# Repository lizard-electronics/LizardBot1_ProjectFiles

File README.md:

# LizardBot1_ProjectFiles
## [In Development...]
Project Files for LizardBot 1 differential-drive ROS2 robot.
ROS2 development repository: https://github.com/lizard-electronics/lizardbot1

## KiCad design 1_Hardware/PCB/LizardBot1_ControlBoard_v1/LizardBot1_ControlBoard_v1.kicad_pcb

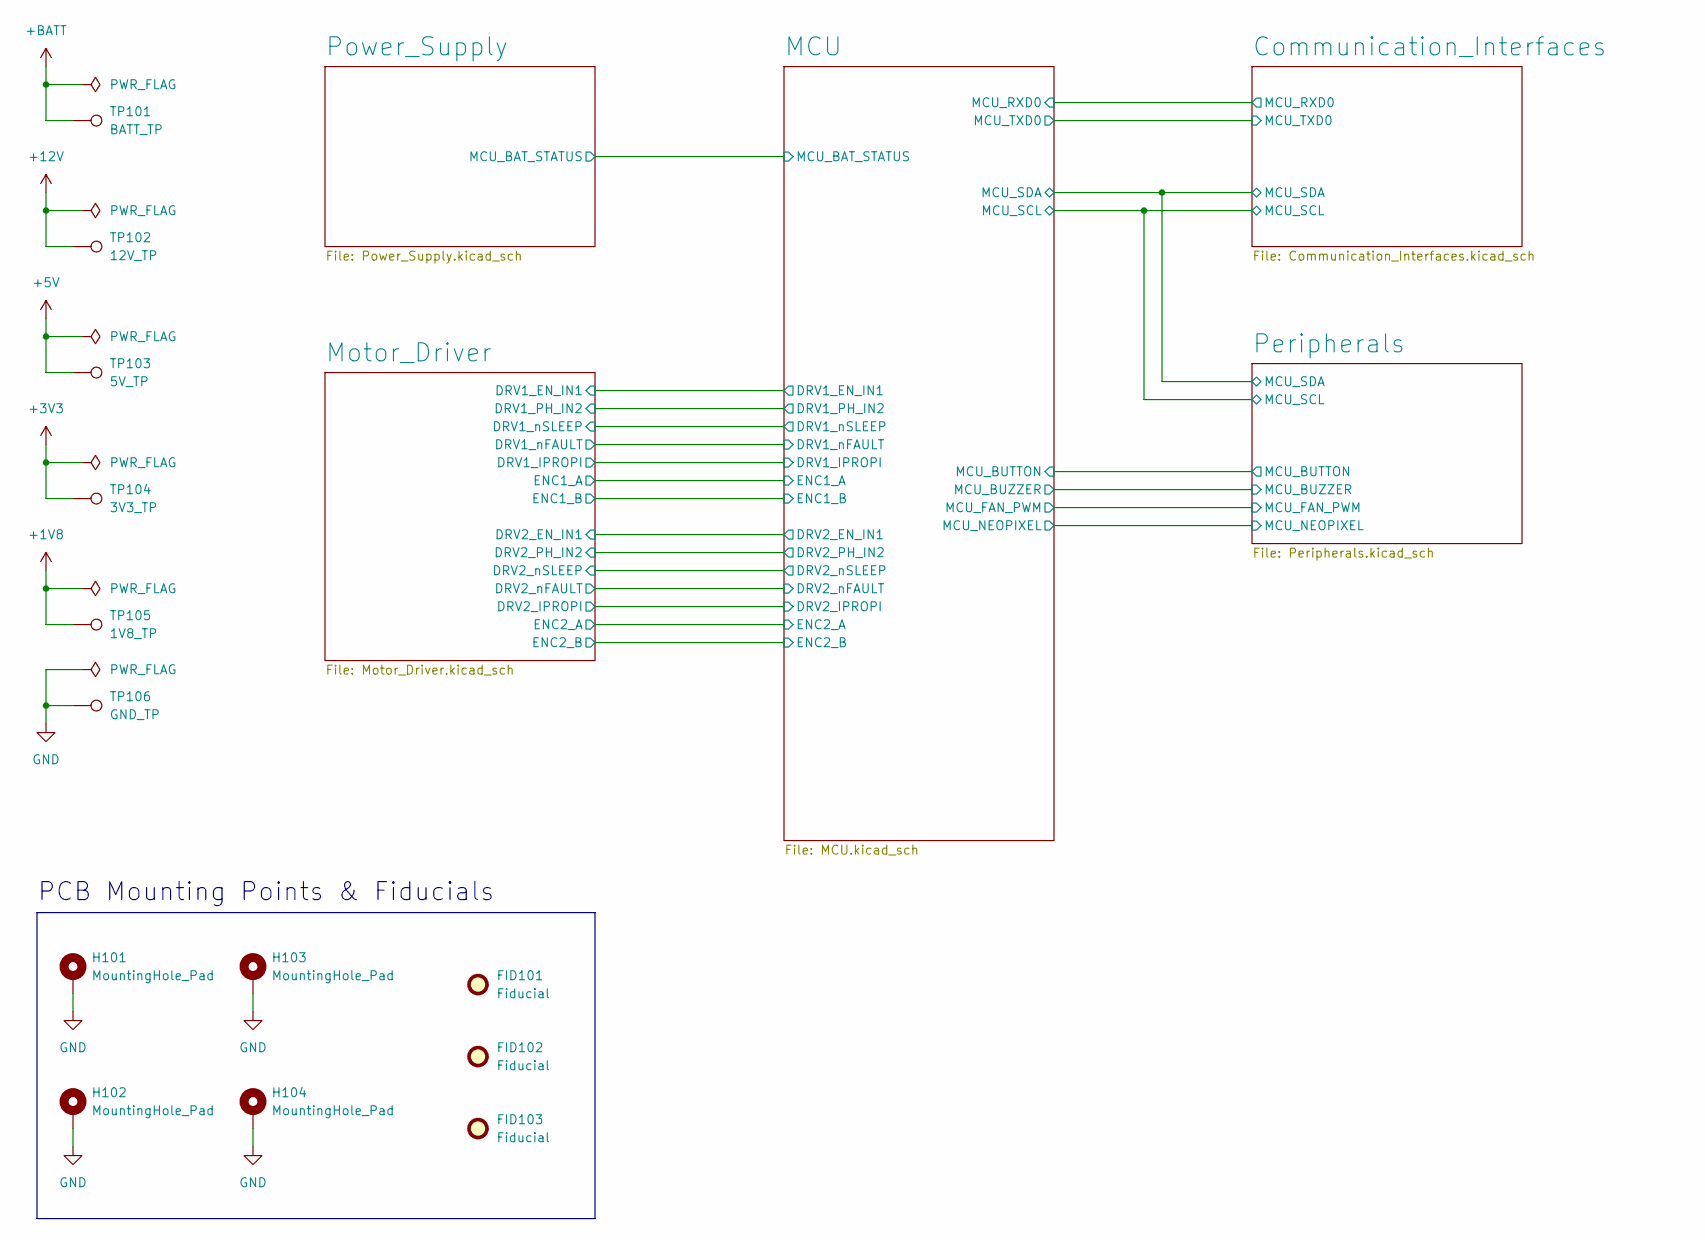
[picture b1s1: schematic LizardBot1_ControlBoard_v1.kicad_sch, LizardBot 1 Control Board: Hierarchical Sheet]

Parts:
FID101, FID102, FID103: Fiducial; Fiducial_1mm_Mask2mm
H101, H102, H103, H104: MountingHole_Pad; MountingHole_3.2mm_M3_Pad_Via
TP101: BATT_TP; TestPoint_Pad_D1.5mm
TP102: 12V_TP; TestPoint_Pad_D1.5mm
TP103: 5V_TP; TestPoint_Pad_D1.5mm
TP104: 3V3_TP; TestPoint_Pad_D1.5mm
TP105: 1V8_TP; TestPoint_Pad_D1.5mm
TP106: GND_TP; TestPoint_Pad_D1.5mm

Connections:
+1V8: TP105.1; also elsewhere on the board
+3V3: TP104.1; also elsewhere on the board
+5V: TP103.1; also elsewhere on the board
+12V: TP102.1; also elsewhere on the board
+BATT: TP101.1; also elsewhere on the board
GND: H101.1, H102.1, H103.1, H104.1, TP106.1; also elsewhere on the board

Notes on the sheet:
PCB Mounting Points & Fiducials

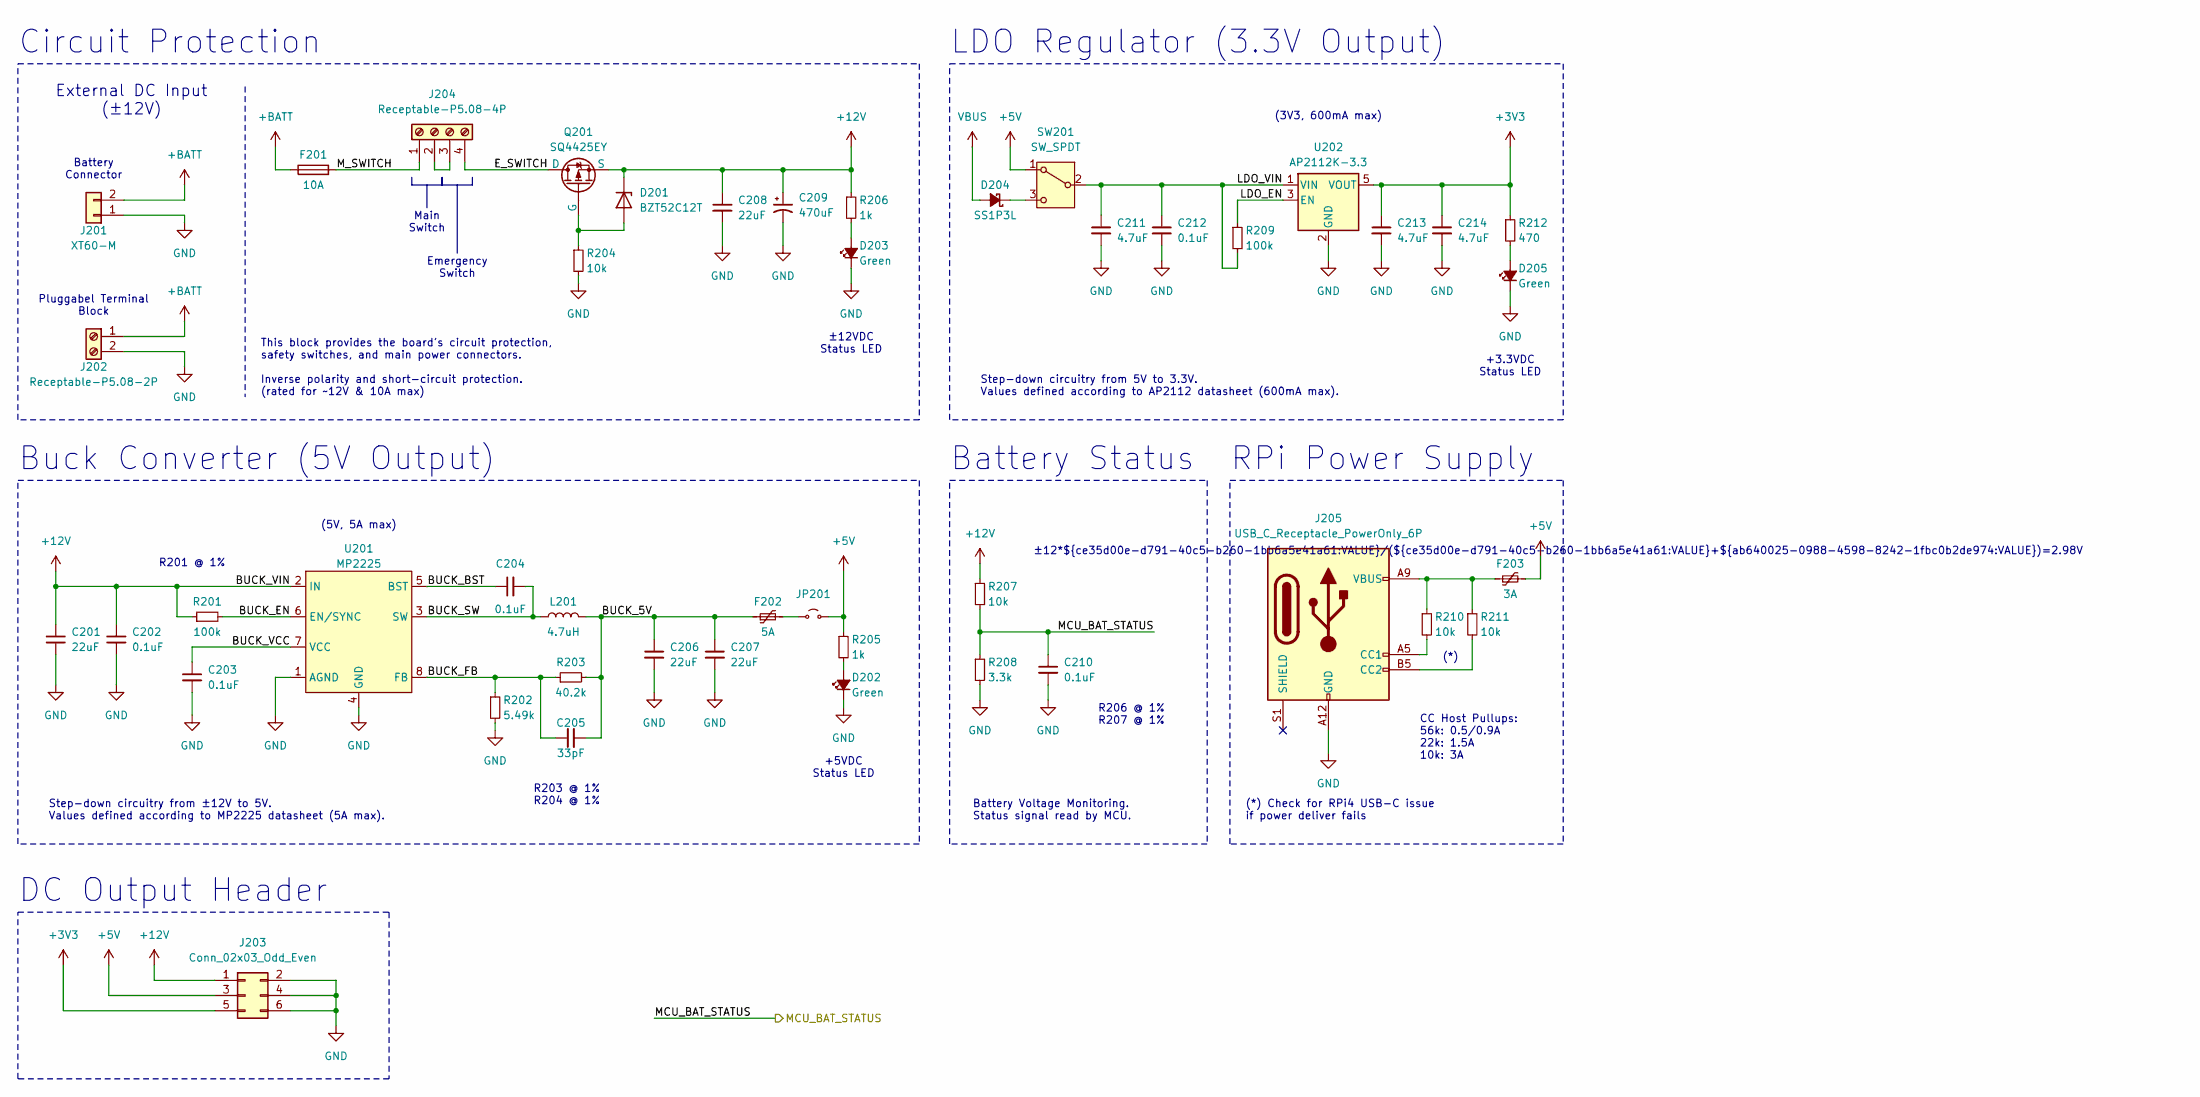
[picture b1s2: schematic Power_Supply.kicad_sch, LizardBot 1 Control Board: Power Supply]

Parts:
C201, C206, C207, C208: 22uF; C_0805_2012Metric_Pad1.18x1.45mm_HandSolder
C202, C212: 0.1uF; C_0805_2012Metric_Pad1.18x1.45mm_HandSolder
C203, C204, C210: 0.1uF; C_0603_1608Metric_Pad1.08x0.95mm_HandSolder
C205: 33pF; C_0603_1608Metric_Pad1.08x0.95mm_HandSolder
C209: 470uF; CP_Elec_8x10
C211, C213, C214: 4.7uF; C_0805_2012Metric_Pad1.18x1.45mm_HandSolder
D201: BZT52C12T; D_SOD-523
D202, D203, D205: Green; LED_0805_2012Metric_Pad1.15x1.40mm_HandSolder
D204: SS1P3L; D_SMP_DO-220AA
F201: 10A; Fuseholder_LittelFuse_5x20mm_0PTF0078P
F202: 5A; Fuse_1812_4532Metric_Pad1.30x3.40mm_HandSolder
F203: 3A; Fuse_1206_3216Metric_Pad1.42x1.75mm_HandSolder
J201: XT60-M; AMASS_XT60PW-M_1x02_P7.20mm_Horizontal
J202: Receptable-P5.08-2P; PhoenixContact_MSTBA_2,5_2-G-5,08_1x02_P5.08mm_Horizontal
J203: Conn_02x03_Odd_Even; PinHeader_2x03_P2.54mm_Vertical
J204: Receptable-P5.08-4P; PhoenixContact_MSTBA_2,5_4-G-5,08_1x04_P5.08mm_Horizontal
J205: USB_C_Receptacle_PowerOnly_6P; USB_C_Receptacle_GCT_USB4085
JP201: Jumper_2_Small_Open; SolderJumper-2_P1.3mm_Open_TrianglePad1.0x1.5mm
L201: 4.7uH; L_Bourns_SRP7028A_7.3x6.6mm
Q201: SQ4425EY; SO-8_3.9x4.9mm_P1.27mm
R201, R209: 100k; R_0805_2012Metric_Pad1.20x1.40mm_HandSolder
R202: 5.49k; R_0805_2012Metric_Pad1.20x1.40mm_HandSolder
R203: 40.2k; R_0805_2012Metric_Pad1.20x1.40mm_HandSolder
R204, R207: 10k; R_0805_2012Metric_Pad1.20x1.40mm_HandSolder
R205, R206: 1k; R_0603_1608Metric_Pad0.98x0.95mm_HandSolder
R208: 3.3k; R_0805_2012Metric_Pad1.20x1.40mm_HandSolder
R210, R211: 10k; R_0603_1608Metric_Pad0.98x0.95mm_HandSolder
R212: 470; R_0603_1608Metric_Pad0.98x0.95mm_HandSolder
SW201: SW_SPDT; SW_Slide_SPDT_Straight_CK_OS102011MS2Q
U201: MP2225; SOT-23-8
U202: AP2112K-3.3; SOT-23-5

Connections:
+3V3: C213.1, C214.1, J203.5, R212.1, U202.5 (VOUT); also elsewhere on the board
+5V: F203.2, J203.3, JP201.2 (B), R205.1, SW201.1 (A); also elsewhere on the board
+12V: C201.1, C202.1, C208.1, C209.1, D201.1 (K), J203.1, Q201.1 (S), Q201.2 (S), Q201.3 (S), R201.1, R206.1, R207.1, U201.2 (IN); also elsewhere on the board
+BATT: F201.1, J201.2, J202.1; also elsewhere on the board
/MCU/MCU_BAT_STATUS: C210.1, R207.2, R208.1; also elsewhere on the board
/Power_Supply/BUCK_5V: C205.2, C206.1, C207.1, F202.1, L201.2, R203.2
/Power_Supply/BUCK_BST: C204.1, U201.5 (BST)
/Power_Supply/BUCK_EN: R201.2, U201.6 (EN/SYNC)
/Power_Supply/BUCK_FB: C205.1, R202.1, R203.1, U201.8 (FB)
/Power_Supply/BUCK_SW: C204.2, L201.1, U201.3 (SW)
/Power_Supply/BUCK_VCC: C203.1, U201.7 (VCC)
/Power_Supply/E_SWITCH: J204.4, Q201.5 (D), Q201.6 (D), Q201.7 (D), Q201.8 (D)
/Power_Supply/LDO_EN: R209.1, U202.3 (EN)
/Power_Supply/LDO_VIN: C211.1, C212.1, R209.2, SW201.2 (B), U202.1 (VIN)
/Power_Supply/M_SWITCH: F201.2, J204.1
GND: C201.2, C202.2, C203.2, C206.2, C207.2, C208.2, C209.2, C210.2, C211.2, C212.2, C213.2, C214.2, D202.1 (K), D203.1 (K), D205.1 (K), J201.1, J202.2, J203.2, J203.4, J203.6, J205.A12 (GND), J205.B12 (GND), R202.2, R204.2, R208.2, U201.1 (AGND), U201.4 (GND), U202.2 (GND); also elsewhere on the board
unnamed: D201.2 (A), Q201.4 (G), R204.1
unnamed: D202.2 (A), R205.2
unnamed: D203.2 (A), R206.2
unnamed: D204.1 (K), SW201.3 (C)
unnamed: D205.2 (A), R212.2
unnamed: F203.1, J205.A9 (VBUS), J205.B9 (VBUS), R210.1, R211.1
unnamed: J204.2, J204.3
unnamed: J205.A5 (CC1), R210.2
unnamed: J205.B5 (CC2), R211.2
unnamed: F202.2, JP201.1 (A)
VBUS: D204.2 (A); also elsewhere on the board

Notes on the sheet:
Circuit Protection
Battery Connector
CC Host Pullups: 56k: 0.5/0.9A 22k: 1.5A 10k: 3A
(3V3, 600mA max)
(*) Check for RPi4 USB-C issue if power deliver fails
±12*${ce35d00e-d791-40c5-b260-1bb6a5e41a61:VALUE}/(${ce35d00e-d791-40c5-b260-1bb6a5e41a61:VALUE}+${ab640025-0988-4598-8242-1fbc0b2de974:VALUE})=2.98V
LDO Regulator (3.3V Output)
Pluggabel Terminal Block
Battery Voltage Monitoring. Status signal read by MCU.
+3.3VDC Status LED
R201 @ 1%
±12VDC Status LED
Battery Status
(5V, 5A max)
External DC Input (±12V)
DC Output Header
(*)
Step-down circuitry from 5V to 3.3V. Values defined according to AP2112 datasheet (600mA max).
This block provides the board's circuit protection, safety switches, and main power connectors. Inverse polarity and short-circuit protection. (rated for ~12V & 10A max)
R203 @ 1% R204 @ 1%
Main Switch
Buck Converter (5V Output)
R206 @ 1% R207 @ 1%
RPi Power Supply
Step-down circuitry from ±12V to 5V. Values defined according to MP2225 datasheet (5A max).
Emergency Switch
+5VDC Status LED

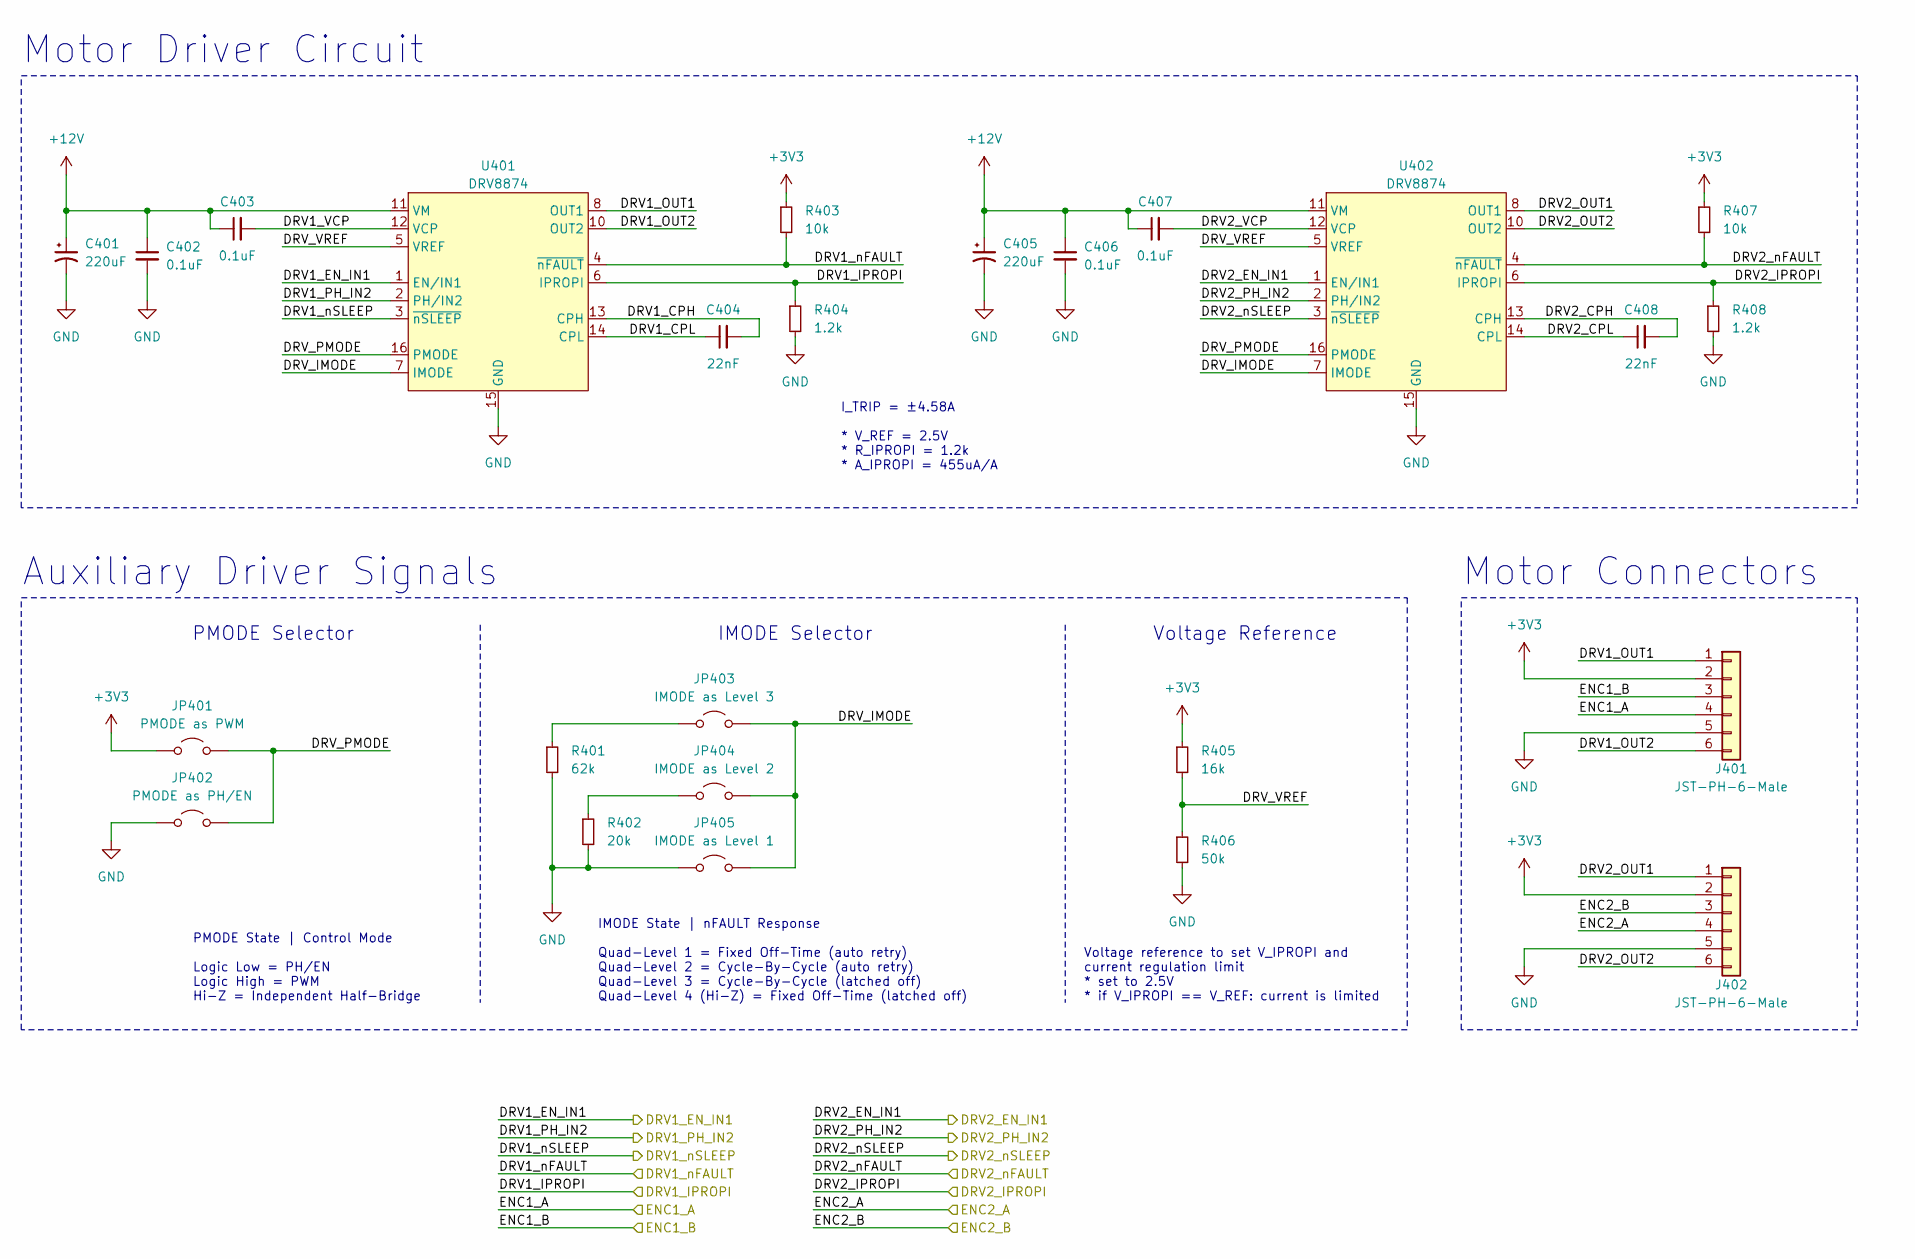
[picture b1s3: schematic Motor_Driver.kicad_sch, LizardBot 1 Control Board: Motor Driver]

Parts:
C401, C405: 220uF; CP_Elec_8x10
C402, C403, C406, C407: 0.1uF; C_0603_1608Metric_Pad1.08x0.95mm_HandSolder
C404, C408: 22nF; C_0805_2012Metric_Pad1.18x1.45mm_HandSolder
J401, J402: JST-PH-6-Male; JST_PH_S6B-PH-K_1x06_P2.00mm_Horizontal
JP401: PMODE as PWM; SolderJumper-2_P1.3mm_Open_TrianglePad1.0x1.5mm
JP402: PMODE as PH/EN; SolderJumper-2_P1.3mm_Open_TrianglePad1.0x1.5mm
JP403: IMODE as Level 3; SolderJumper-2_P1.3mm_Open_TrianglePad1.0x1.5mm
JP404: IMODE as Level 2; SolderJumper-2_P1.3mm_Open_TrianglePad1.0x1.5mm
JP405: IMODE as Level 1; SolderJumper-2_P1.3mm_Open_TrianglePad1.0x1.5mm
R401: 62k; R_0805_2012Metric_Pad1.20x1.40mm_HandSolder
R402: 20k; R_0805_2012Metric_Pad1.20x1.40mm_HandSolder
R403, R407: 10k; R_0805_2012Metric_Pad1.20x1.40mm_HandSolder
R404, R408: 1.2k; R_0805_2012Metric_Pad1.20x1.40mm_HandSolder
R405: 16k; R_0805_2012Metric_Pad1.20x1.40mm_HandSolder
R406: 50k; R_0805_2012Metric_Pad1.20x1.40mm_HandSolder
U401, U402: DRV8874; HTSSOP-16-1EP_4.4x5mm_P0.65mm_EP3.4x5mm_Mask3x3mm_ThermalVi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

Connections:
+3V3: J401.2, J402.2, JP401.1 (A), R403.1, R405.1, R407.1; also elsewhere on the board
+12V: C401.1, C402.1, C403.1, C405.1, C406.1, C407.1, U401.11 (VM), U402.11 (VM); also elsewhere on the board
/MCU/DRV1_EN_IN1: U401.1 (EN/IN1); also elsewhere on the board
/MCU/DRV1_IPROPI: R404.1, U401.6 (IPROPI); also elsewhere on the board
/MCU/DRV1_PH_IN2: U401.2 (PH/IN2); also elsewhere on the board
/MCU/DRV1_nFAULT: R403.2, U401.4 (~nFAULT); also elsewhere on the board
/MCU/DRV1_nSLEEP: U401.3 (~nSLEEP); also elsewhere on the board
/MCU/DRV2_EN_IN1: U402.1 (EN/IN1); also elsewhere on the board
/MCU/DRV2_IPROPI: R408.1, U402.6 (IPROPI); also elsewhere on the board
/MCU/DRV2_PH_IN2: U402.2 (PH/IN2); also elsewhere on the board
/MCU/DRV2_nFAULT: R407.2, U402.4 (~nFAULT); also elsewhere on the board
/MCU/DRV2_nSLEEP: U402.3 (~nSLEEP); also elsewhere on the board
/MCU/ENC1_A: J401.4; also elsewhere on the board
/MCU/ENC1_B: J401.3; also elsewhere on the board
/MCU/ENC2_A: J402.4; also elsewhere on the board
/MCU/ENC2_B: J402.3; also elsewhere on the board
/Motor_Driver/DRV1_CPH: C404.2, U401.13 (CPH)
/Motor_Driver/DRV1_CPL: C404.1, U401.14 (CPL)
/Motor_Driver/DRV1_OUT1: J401.1, U401.8 (OUT1)
/Motor_Driver/DRV1_OUT2: J401.6, U401.10 (OUT2)
/Motor_Driver/DRV1_VCP: C403.2, U401.12 (VCP)
/Motor_Driver/DRV2_CPH: C408.2, U402.13 (CPH)
/Motor_Driver/DRV2_CPL: C408.1, U402.14 (CPL)
/Motor_Driver/DRV2_OUT1: J402.1, U402.8 (OUT1)
/Motor_Driver/DRV2_OUT2: J402.6, U402.10 (OUT2)
/Motor_Driver/DRV2_VCP: C407.2, U402.12 (VCP)
/Motor_Driver/DRV_IMODE: JP403.2 (B), JP404.2 (B), JP405.2 (B), U401.7 (IMODE), U402.7 (IMODE)
/Motor_Driver/DRV_PMODE: JP401.2 (B), JP402.2 (B), U401.16 (PMODE), U402.16 (PMODE)
/Motor_Driver/DRV_VREF: R405.2, R406.1, U401.5 (VREF), U402.5 (VREF)
GND: C401.2, C402.2, C405.2, C406.2, J401.5, J402.5, JP402.1 (A), JP405.1 (A), R401.2, R402.2, R404.2, R406.2, R408.2, U401.9 (PGND), U401.15 (GND), U401.17 (PAD), U402.9 (PGND), U402.15 (GND), U402.17 (PAD); also elsewhere on the board
unnamed: JP403.1 (A), R401.1
unnamed: JP404.1 (A), R402.1

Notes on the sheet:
I_TRIP = ±4.58A * V_REF = 2.5V * R_IPROPI = 1.2k * A_IPROPI = 455uA/A
IMODE State | nFAULT Response Quad-Level 1 = Fixed Off-Time (auto retry) Quad-Level 2 = Cycle-By-Cycle (auto retry) Quad-Level 3 = Cycle-By-Cycle (latched off) Quad-Level 4 (Hi-Z) = Fixed Off-Time (latched off)
Voltage Reference
IMODE Selector
Motor Driver Circuit
PMODE Selector
PMODE State | Control Mode Logic Low = PH/EN Logic High = PWM Hi-Z = Independent Half-Bridge
Auxiliary Driver Signals
Motor Connectors
Voltage reference to set V_IPROPI and current regulation limit * set to 2.5V * if V_IPROPI == V_REF: current is limited

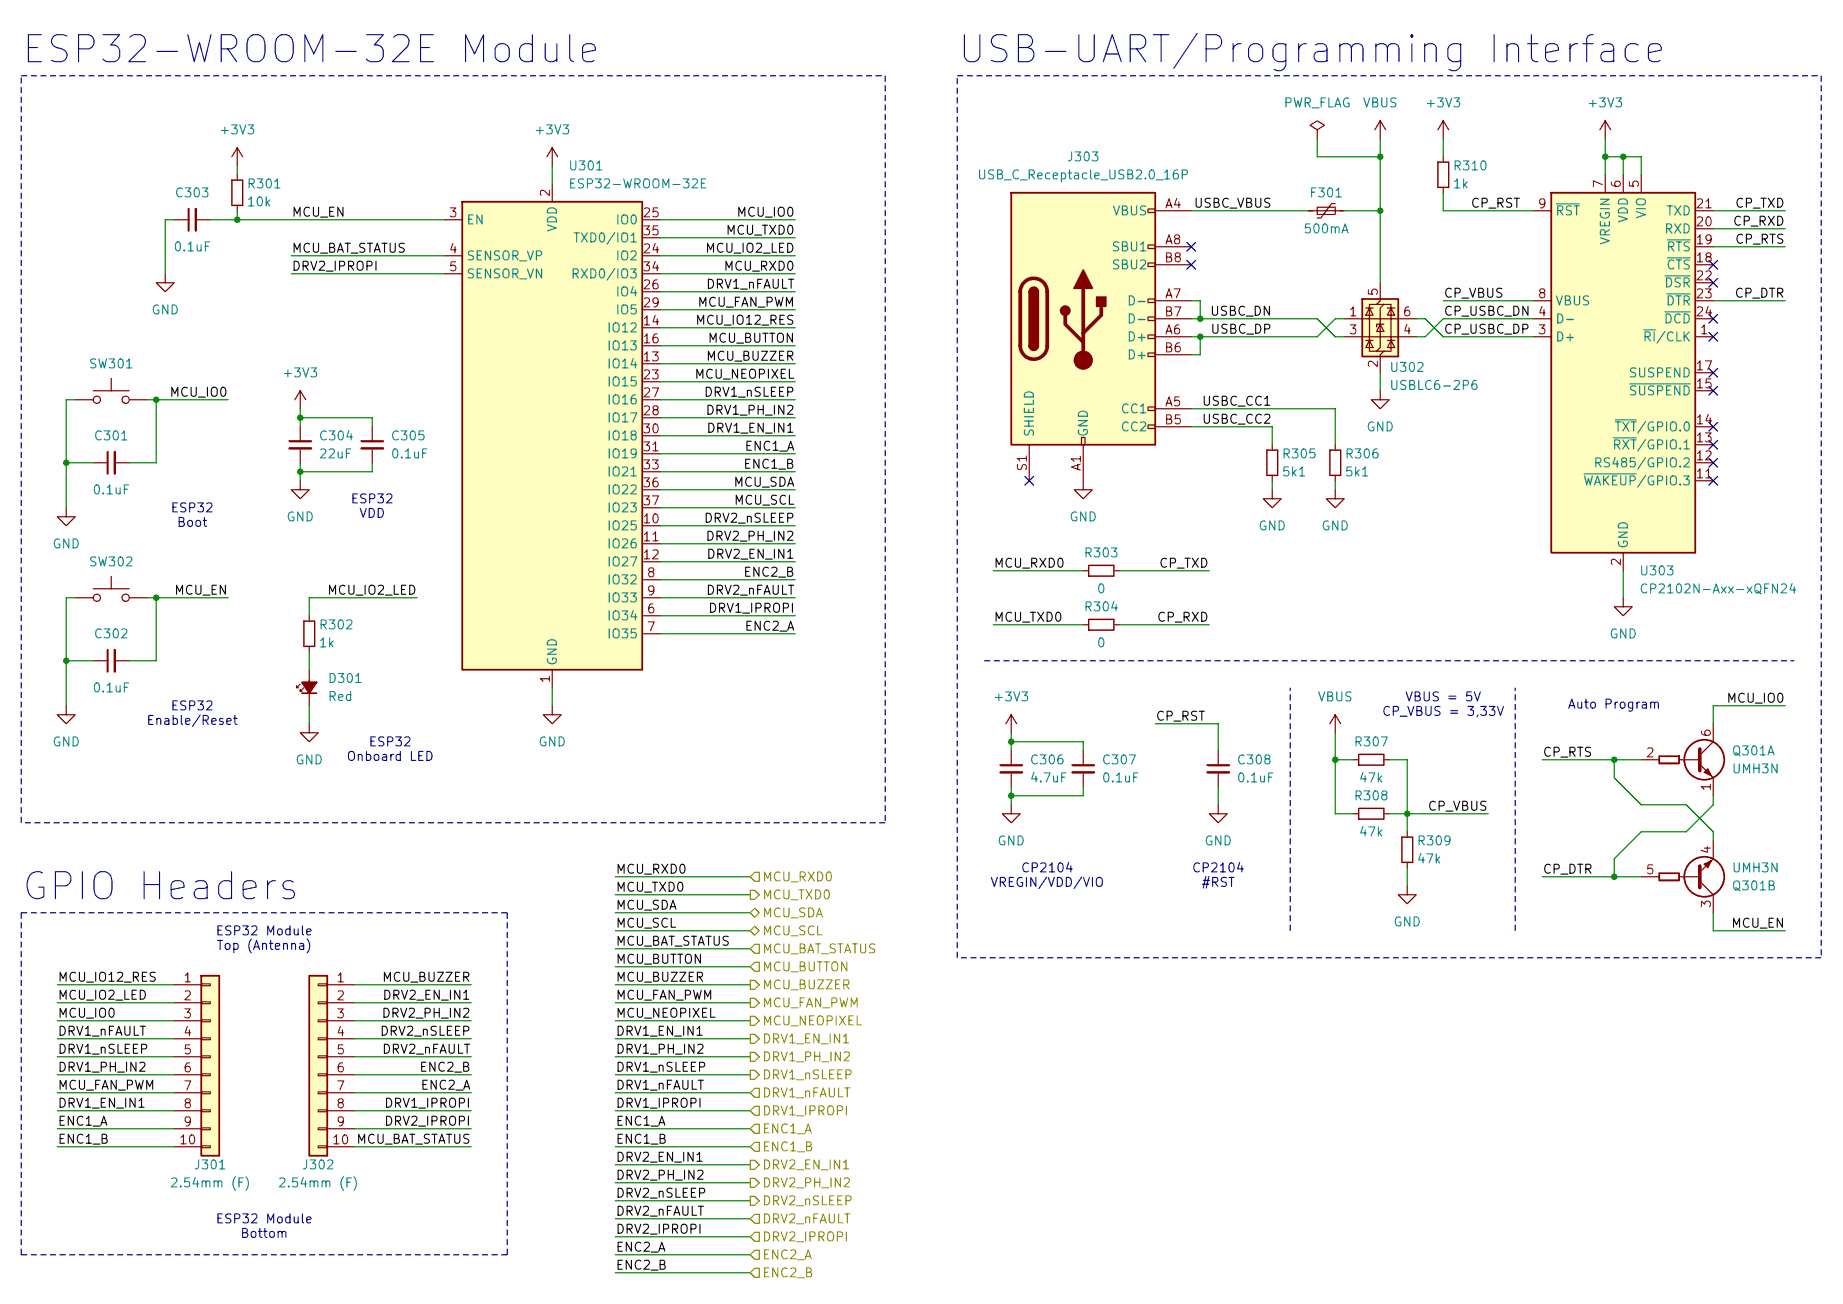
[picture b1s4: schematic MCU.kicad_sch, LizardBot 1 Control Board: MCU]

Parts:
C301, C302, C303: 0.1uF; C_0603_1608Metric_Pad1.08x0.95mm_HandSolder
C304: 22uF; C_0805_2012Metric_Pad1.18x1.45mm_HandSolder
C305, C307, C308: 0.1uF; C_0805_2012Metric_Pad1.18x1.45mm_HandSolder
C306: 4.7uF; C_0805_2012Metric_Pad1.18x1.45mm_HandSolder
D301: Red; LED_1206_3216Metric_Pad1.42x1.75mm_HandSolder
F301: 500mA; Fuse_1206_3216Metric_Pad1.42x1.75mm_HandSolder
J301, J302: 2.54mm (F); PinHeader_1x10_P2.54mm_Vertical
J303: USB_C_Receptacle_USB2.0_16P; USB_C_Receptacle_GCT_USB4085
Q301: UMH3N; SOT-363_SC-70-6
R301: 10k; R_0603_1608Metric_Pad0.98x0.95mm_HandSolder
R302, R310: 1k; R_0603_1608Metric_Pad0.98x0.95mm_HandSolder
R303, R304: 0; R_0603_1608Metric_Pad0.98x0.95mm_HandSolder
R305, R306: 5k1; R_0603_1608Metric_Pad0.98x0.95mm_HandSolder
R307, R308, R309: 47k; R_0603_1608Metric_Pad0.98x0.95mm_HandSolder
SW301, SW302: SW_Push; SW_SPST_TL3342
U301: ESP32-WROOM-32E; ESP32-WROOM-32D
U302: USBLC6-2P6; SOT-666
U303: CP2102N-Axx-xQFN24; QFN-24-1EP_4x4mm_P0.5mm_EP2.6x2.6mm

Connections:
+3V3: C304.1, C305.1, C306.1, C307.1, R301.1, R310.1, U301.2 (VDD), U303.5 (VIO), U303.6 (VDD), U303.7 (VREGIN); also elsewhere on the board
/Communication_Interfaces/MCU_RXD0: R303.1, U301.34 (RXD0/IO3); also elsewhere on the board
/Communication_Interfaces/MCU_SCL: U301.37 (IO23); also elsewhere on the board
/Communication_Interfaces/MCU_SDA: U301.36 (IO22); also elsewhere on the board
/Communication_Interfaces/MCU_TXD0: R304.1, U301.35 (TXD0/IO1); also elsewhere on the board
/MCU/CP_DTR: Q301.1 (E1), Q301.5 (B2), U303.23 (~DTR)
/MCU/CP_RST: C308.1, R310.2, U303.9 (~RST)
/MCU/CP_RTS: Q301.2 (B1), Q301.4 (E2), U303.19 (~RTS)
/MCU/CP_RXD: R304.2, U303.20 (RXD)
/MCU/CP_TXD: R303.2, U303.21 (TXD)
/MCU/CP_USBC_DN: U302.4 (I/O2), U303.4 (D-)
/MCU/CP_USBC_DP: U302.6 (I/O1), U303.3 (D+)
/MCU/CP_VBUS: R307.2, R308.2, R309.1, U303.8 (VBUS)
/MCU/DRV1_EN_IN1: J301.8, U301.30 (IO18); also elsewhere on the board
/MCU/DRV1_IPROPI: J302.8, U301.6 (IO34); also elsewhere on the board
/MCU/DRV1_PH_IN2: J301.6, U301.28 (IO17); also elsewhere on the board
/MCU/DRV1_nFAULT: J301.4, U301.26 (IO4); also elsewhere on the board
/MCU/DRV1_nSLEEP: J301.5, U301.27 (IO16); also elsewhere on the board
/MCU/DRV2_EN_IN1: J302.2, U301.12 (IO27); also elsewhere on the board
/MCU/DRV2_IPROPI: J302.9, U301.5 (SENSOR_VN); also elsewhere on the board
/MCU/DRV2_PH_IN2: J302.3, U301.11 (IO26); also elsewhere on the board
/MCU/DRV2_nFAULT: J302.5, U301.9 (IO33); also elsewhere on the board
/MCU/DRV2_nSLEEP: J302.4, U301.10 (IO25); also elsewhere on the board
/MCU/ENC1_A: J301.9, U301.31 (IO19); also elsewhere on the board
/MCU/ENC1_B: J301.10, U301.33 (IO21); also elsewhere on the board
/MCU/ENC2_A: J302.7, U301.7 (IO35); also elsewhere on the board
/MCU/ENC2_B: J302.6, U301.8 (IO32); also elsewhere on the board
/MCU/MCU_BAT_STATUS: J302.10, U301.4 (SENSOR_VP); also elsewhere on the board
/MCU/MCU_BUTTON: U301.16 (IO13); also elsewhere on the board
/MCU/MCU_BUZZER: J302.1, U301.13 (IO14); also elsewhere on the board
/MCU/MCU_EN: C302.2, C303.2, Q301.3 (C2), R301.2, SW302.2, U301.3 (EN)
/MCU/MCU_FAN_PWM: J301.7, U301.29 (IO5); also elsewhere on the board
/MCU/MCU_IO0: C301.2, J301.3, Q301.6 (C1), SW301.2, U301.25 (IO0)
/MCU/MCU_IO2_LED: J301.2, R302.1, U301.24 (IO2)
/MCU/MCU_IO12_RES: J301.1, U301.14 (IO12)
/MCU/MCU_NEOPIXEL: U301.23 (IO15); also elsewhere on the board
/MCU/USBC_CC1: J303.A5 (CC1), R306.1
/MCU/USBC_CC2: J303.B5 (CC2), R305.1
/MCU/USBC_DN: J303.A7 (D-), J303.B7 (D-), U302.3 (I/O2)
/MCU/USBC_DP: J303.A6 (D+), J303.B6 (D+), U302.1 (I/O1)
/MCU/USBC_VBUS: F301.1, J303.A4 (VBUS), J303.A9 (VBUS), J303.B4 (VBUS), J303.B9 (VBUS)
GND: C301.1, C302.1, C303.1, C304.2, C305.2, C306.2, C307.2, C308.2, D301.1 (K), J303.A1 (GND), J303.A12 (GND), J303.B1 (GND), J303.B12 (GND), R305.2, R306.2, R309.2, SW301.1, SW302.1, U301.1 (GND), U301.15 (GND), U301.38 (GND), U301.39 (GND), U302.2 (GND), U303.2 (GND), U303.25 (GND); also elsewhere on the board
unnamed: D301.2 (A), R302.2
VBUS: F301.2, R307.1, R308.1, U302.5 (VBUS); also elsewhere on the board

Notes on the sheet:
ESP32 Module Top (Antenna)
ESP32 VDD
Auto Program
CP2104 VREGIN/VDD/VIO
ESP32-WROOM-32E Module
CP2104 #RST
GPIO Headers
USB-UART/Programming Interface
ESP32 Onboard LED
ESP32 Enable/Reset
VBUS = 5V CP_VBUS = 3,33V
ESP32 Boot
ESP32 Module Bottom

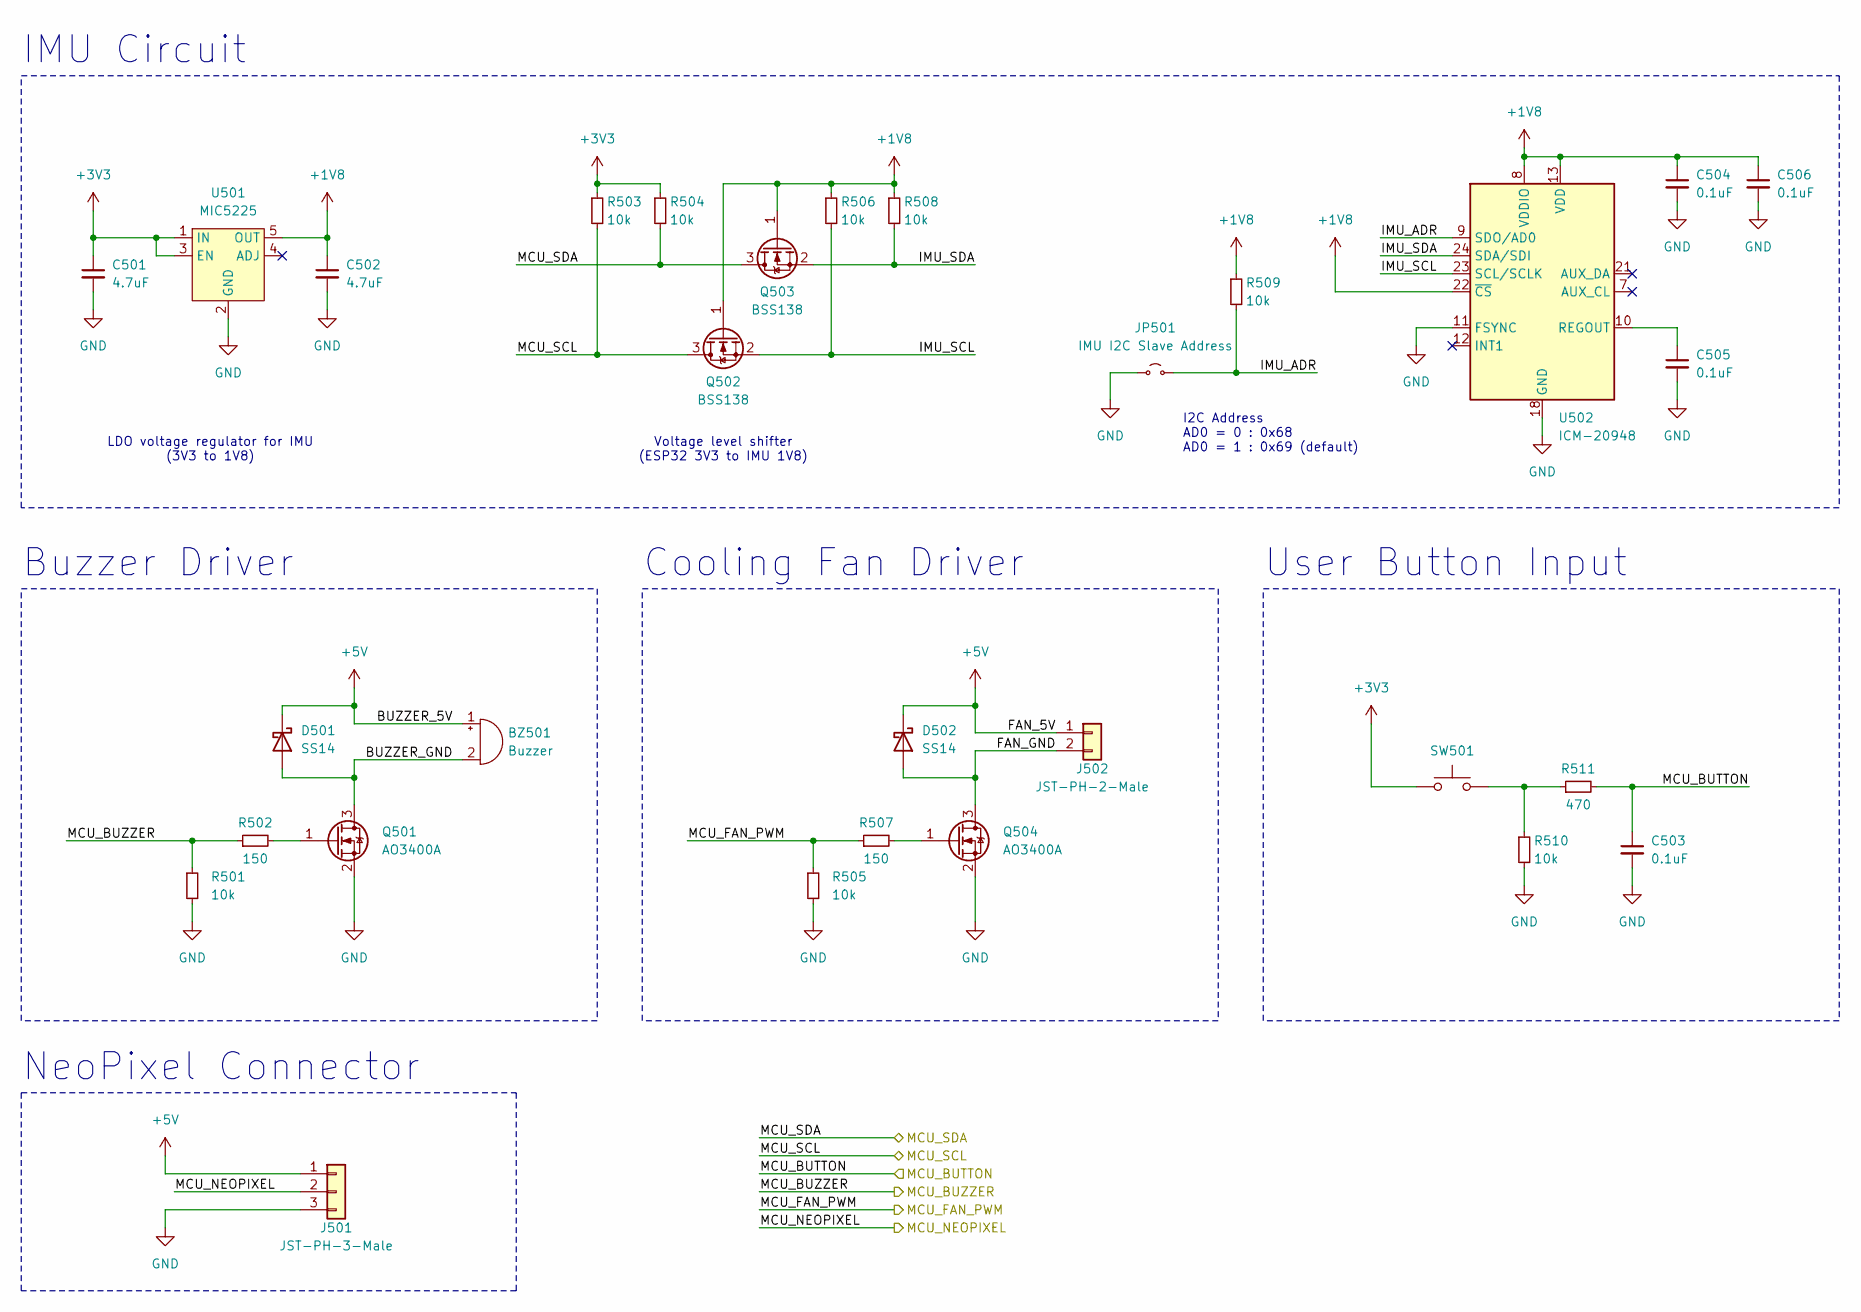
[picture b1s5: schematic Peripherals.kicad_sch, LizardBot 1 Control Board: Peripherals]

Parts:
BZ501: Buzzer; Buzzer_12x9.5RM7.6
C501, C502: 4.7uF; C_0805_2012Metric_Pad1.18x1.45mm_HandSolder
C503, C504, C505, C506: 0.1uF; C_0603_1608Metric_Pad1.08x0.95mm_HandSolder
D501, D502: SS14; D_SMA
J501: JST-PH-3-Male; JST_PH_S3B-PH-K_1x03_P2.00mm_Horizontal
J502: JST-PH-2-Male; JST_PH_S2B-PH-K_1x02_P2.00mm_Horizontal
JP501: IMU I2C Slave Address; SolderJumper-2_P1.3mm_Open_TrianglePad1.0x1.5mm
Q501, Q504: AO3400A; SOT-23
Q502, Q503: BSS138; SOT-23
R501, R505: 10k; R_0805_2012Metric_Pad1.20x1.40mm_HandSolder
R502, R507: 150; R_0805_2012Metric_Pad1.20x1.40mm_HandSolder
R503, R504, R506, R508, R509, R510: 10k; R_0603_1608Metric_Pad0.98x0.95mm_HandSolder
R511: 470; R_0603_1608Metric_Pad0.98x0.95mm_HandSolder
SW501: SW_Push; SW_PUSH-12mm
U501: MIC5225; SOT-23-5_HandSoldering
U502: ICM-20948; InvenSense_QFN-24_3x3mm_P0.4mm

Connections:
+1V8: C502.1, C504.1, C506.1, Q502.1 (G), Q503.1 (G), R506.1, R508.1, R509.1, U501.5 (OUT), U502.8 (VDDIO), U502.13 (VDD), U502.22 (~CS); also elsewhere on the board
+3V3: C501.1, R503.1, R504.1, SW501.1, U501.1 (IN), U501.3 (EN); also elsewhere on the board
+5V: BZ501.1 (+), D501.1 (K), D502.1 (K), J501.1, J502.1; also elsewhere on the board
/Communication_Interfaces/MCU_SCL: Q502.3 (D), R503.2; also elsewhere on the board
/Communication_Interfaces/MCU_SDA: Q503.3 (D), R504.2; also elsewhere on the board
/MCU/MCU_BUTTON: C503.1, R511.2; also elsewhere on the board
/MCU/MCU_BUZZER: R501.1, R502.1; also elsewhere on the board
/MCU/MCU_FAN_PWM: R505.1, R507.1; also elsewhere on the board
/MCU/MCU_NEOPIXEL: J501.2; also elsewhere on the board
/Peripherals/BUZZER_GND: BZ501.2 (-), D501.2 (A), Q501.3 (D)
/Peripherals/FAN_GND: D502.2 (A), J502.2, Q504.3 (D)
/Peripherals/IMU_ADR: JP501.2 (B), R509.2, U502.9 (SDO/AD0)
/Peripherals/IMU_SCL: Q502.2 (S), R506.2, U502.23 (SCL/SCLK)
/Peripherals/IMU_SDA: Q503.2 (S), R508.2, U502.24 (SDA/SDI)
GND: C501.2, C502.2, C503.2, C504.2, C505.2, C506.2, J501.3, JP501.1 (A), Q501.2 (S), Q504.2 (S), R501.2, R505.2, R510.2, U501.2 (GND), U502.11 (FSYNC), U502.18 (GND), U502.20 (GND); also elsewhere on the board
unnamed: Q501.1 (G), R502.2
unnamed: Q504.1 (G), R507.2
unnamed: R510.1, R511.1, SW501.2
unnamed: C505.1, U502.10 (REGOUT)

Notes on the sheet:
IMU Circuit
I2C Address AD0 = 0 : 0x68 AD0 = 1 : 0x69 (default)
NeoPixel Connector
Voltage level shifter (ESP32 3V3 to IMU 1V8)
LDO voltage regulator for IMU (3V3 to 1V8)
User Button Input
Cooling Fan Driver
Buzzer Driver

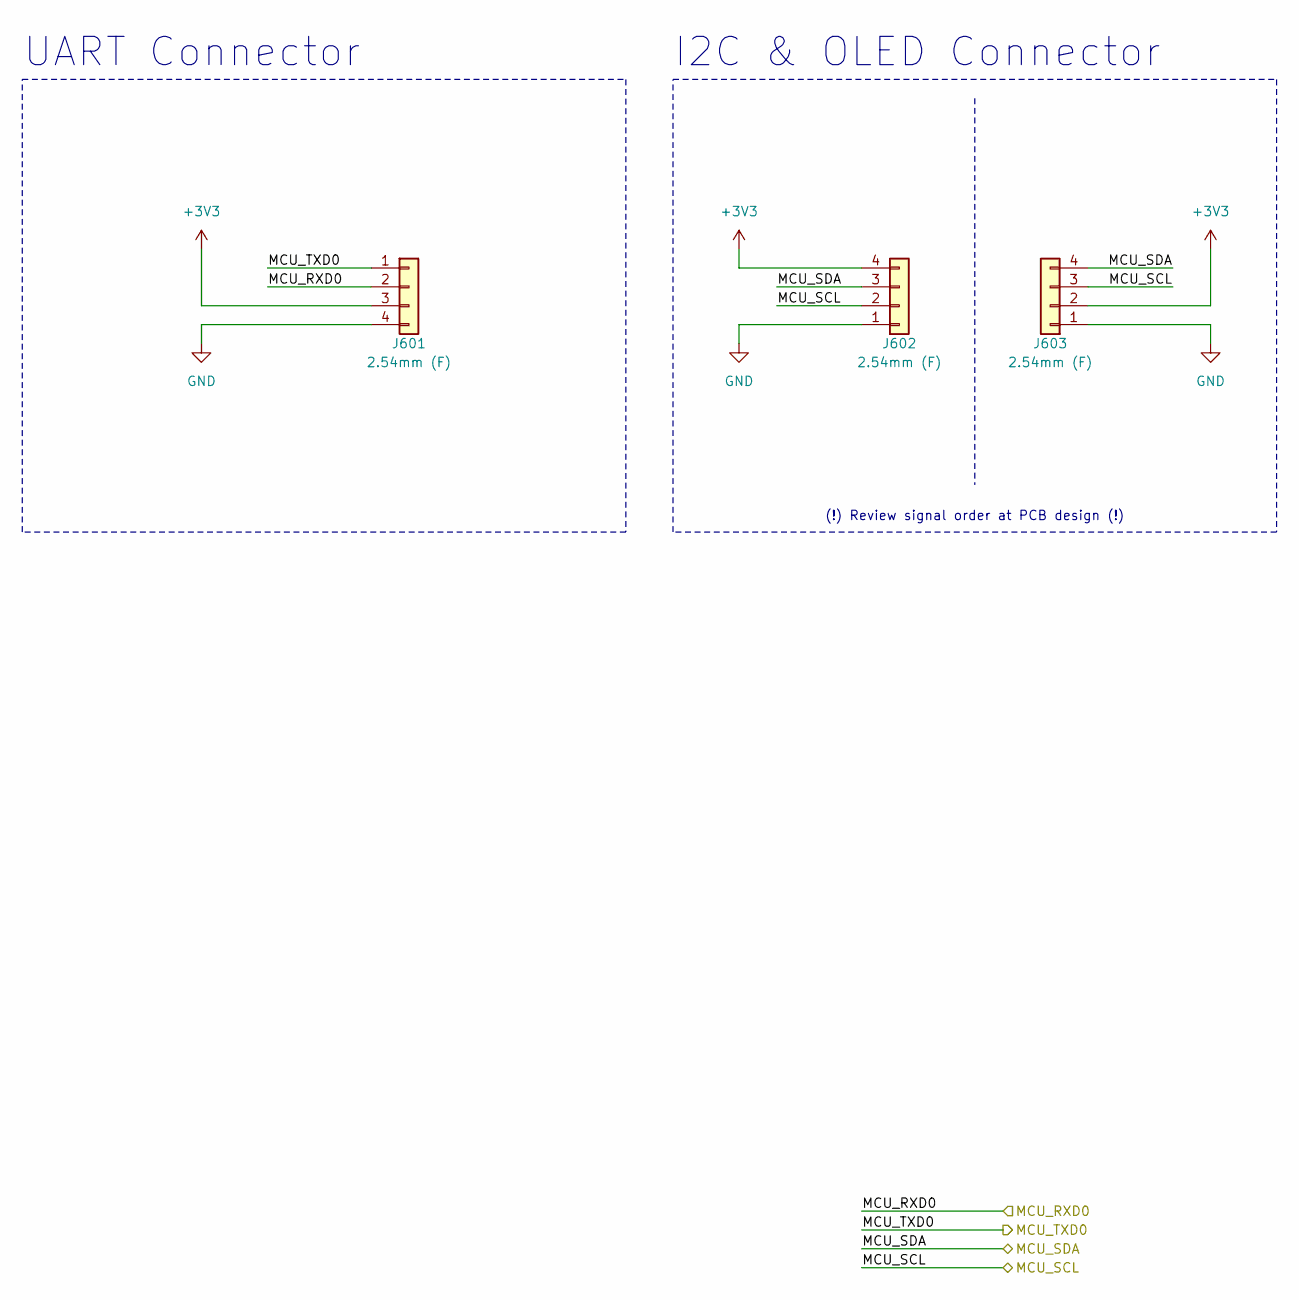
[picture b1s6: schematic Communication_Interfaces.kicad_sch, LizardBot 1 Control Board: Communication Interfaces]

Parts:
J601, J602, J603: 2.54mm (F); PinHeader_1x04_P2.54mm_Vertical

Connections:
+3V3: J601.3, J602.4, J603.2; also elsewhere on the board
/Communication_Interfaces/MCU_RXD0: J601.2; also elsewhere on the board
/Communication_Interfaces/MCU_SCL: J602.2, J603.3; also elsewhere on the board
/Communication_Interfaces/MCU_SDA: J602.3, J603.4; also elsewhere on the board
/Communication_Interfaces/MCU_TXD0: J601.1; also elsewhere on the board
GND: J601.4, J602.1, J603.1; also elsewhere on the board

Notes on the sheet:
UART Connector
(!) Review signal order at PCB design (!)
I2C & OLED Connector
